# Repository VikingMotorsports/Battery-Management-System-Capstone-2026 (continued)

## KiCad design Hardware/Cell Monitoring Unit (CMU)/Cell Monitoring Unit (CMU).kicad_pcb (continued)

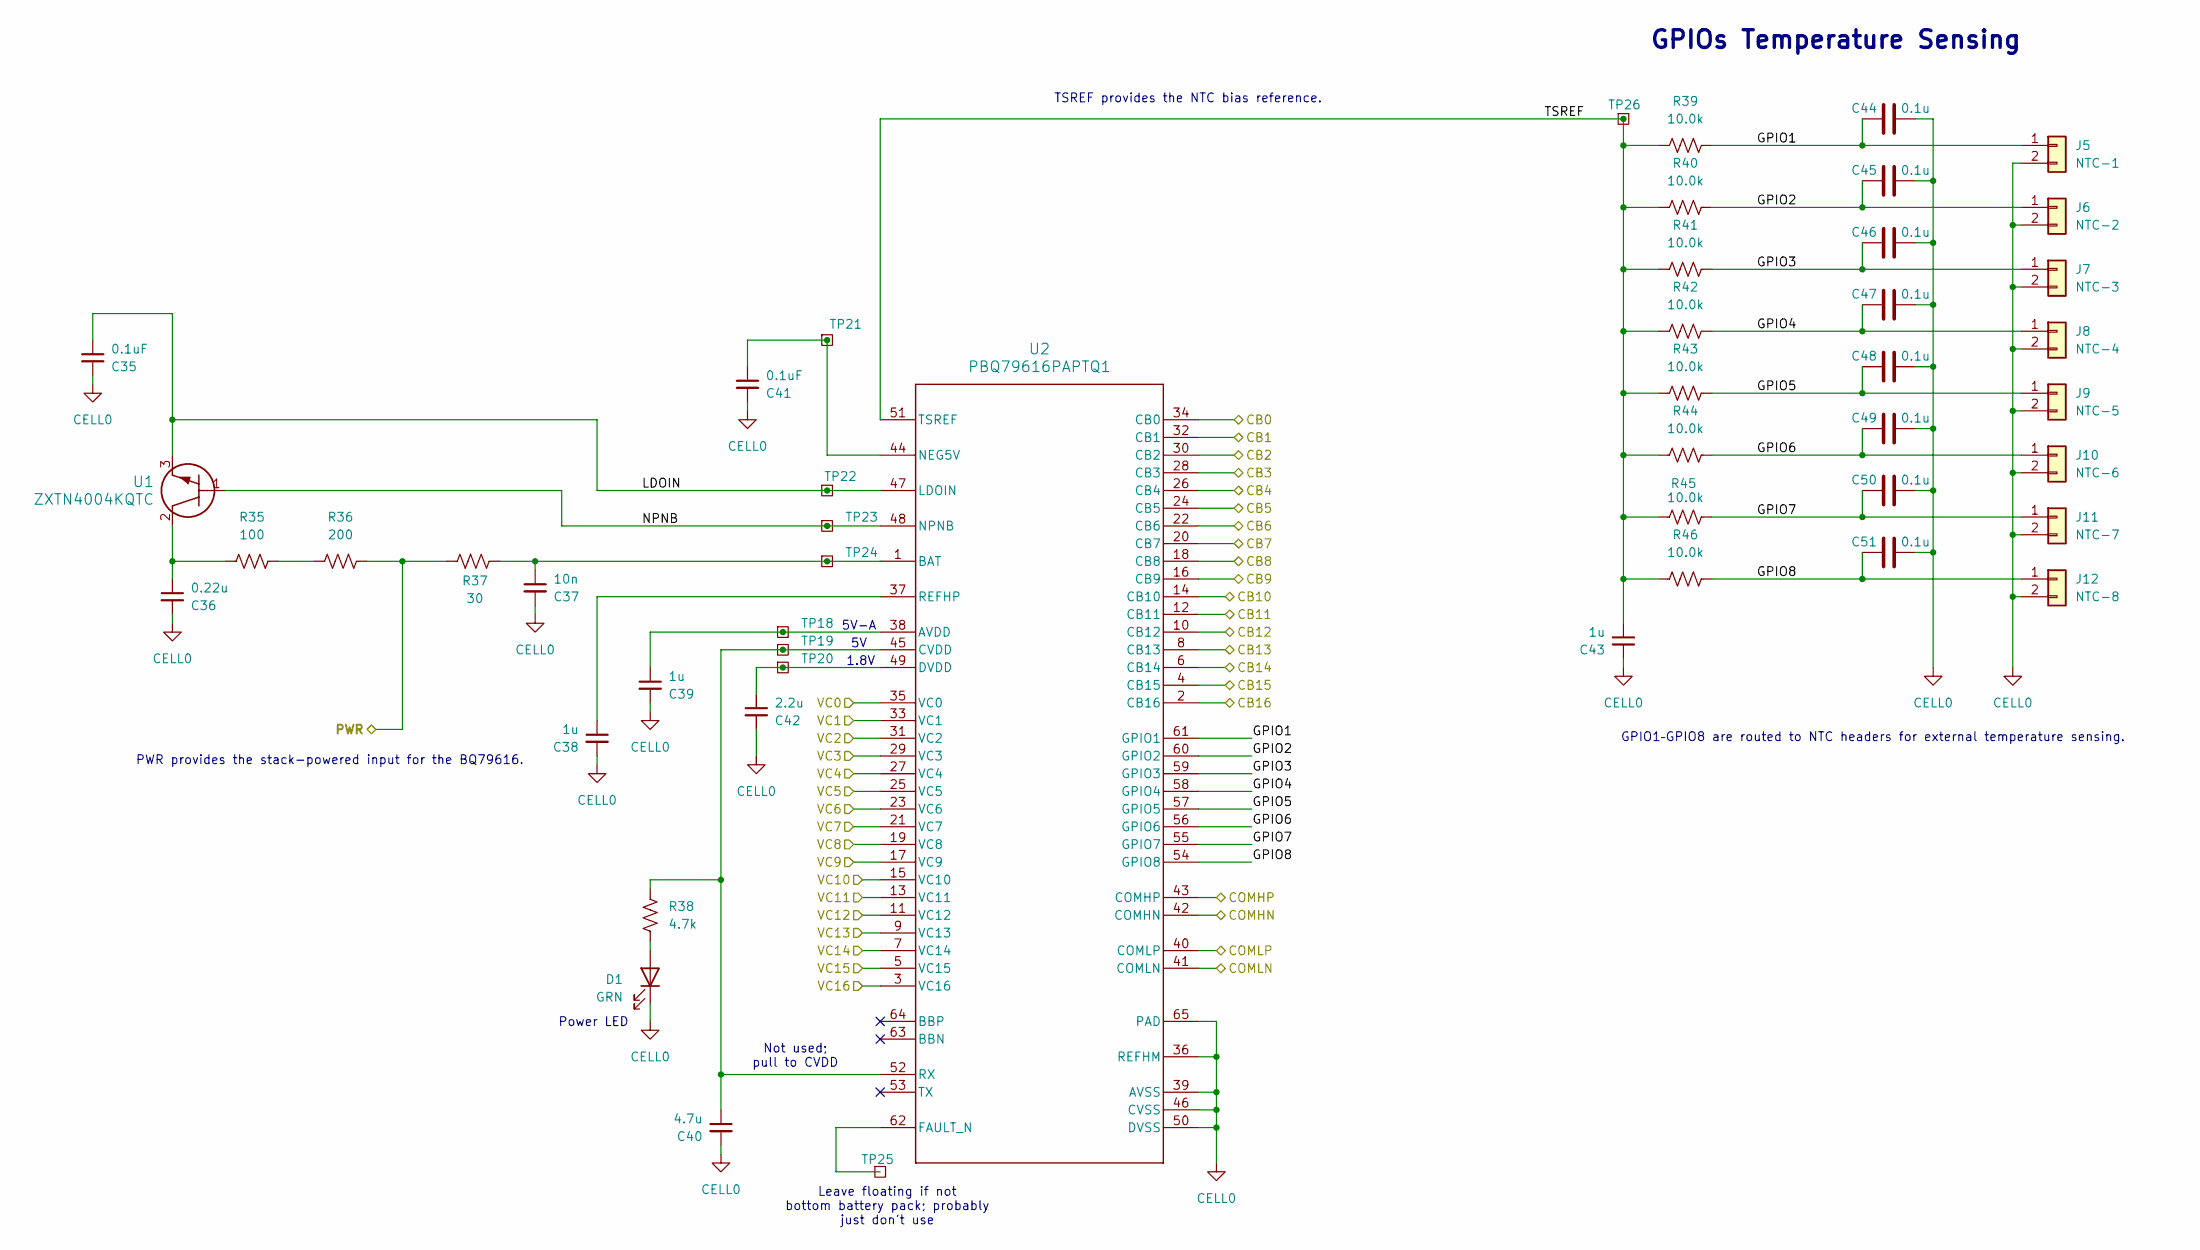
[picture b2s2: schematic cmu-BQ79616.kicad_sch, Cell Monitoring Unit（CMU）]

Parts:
C35, C41: 0.1uF; C_0805_2012Metric; MPN C0805X104K050T
C36: 0.22u; C_0805_2012Metric; MPN 885382207008
C37: 10n; C_0805_2012Metric; MPN C0805C103K5RECAUTO
C38, C39, C43: 1u; C_0805_2012Metric; MPN C0805C105K5RACTU
C40: 4.7u; C_0805_2012Metric; MPN C0805X475K025T
C42: 2.2u; C_0805_2012Metric; MPN 885012207079
C44, C45, C46, C47, C48, C49, C50, C51: 0.1u; C_0805_2012Metric; MPN C0805X104K050T
D1: GRN; LED_0805_2012Metric; MPN LTST-C170KGKT
J5: NTC-1; PinHeader_1x02_P2.54mm_Vertical; MPN 61300211121
J6: NTC-2; PinHeader_1x02_P2.54mm_Vertical; MPN 61300211121
J7: NTC-3; PinHeader_1x02_P2.54mm_Vertical; MPN 61300211121
J8: NTC-4; PinHeader_1x02_P2.54mm_Vertical; MPN 61300211121
J9: NTC-5; PinHeader_1x02_P2.54mm_Vertical; MPN 61300211121
J10: NTC-6; PinHeader_1x02_P2.54mm_Vertical; MPN 61300211121
J11: NTC-7; PinHeader_1x02_P2.54mm_Vertical; MPN 61300211121
J12: NTC-8; PinHeader_1x02_P2.54mm_Vertical; MPN 61300211121
R35: 100; R_2010_5025Metric; MPN RMCF2010FT100R
R36: 200; R_2010_5025Metric; MPN RMCF2010FT200R
R37: 30; R_2010_5025Metric; MPN RC2010FK-0730RL
R38: 4.7k; R_2010_5025Metric; MPN RC2010FK-074K7L
R39, R40, R41, R42, R43, R44, R45, R46: 10.0k; R_0805_2012Metric; MPN RC0805FR-0710KL
TP18, TP19, TP20, TP21, TP22, TP23, TP24, TP25, TP26: TestPoint_Square; TestPoint_THTPad_D1.5mm_Drill0.7mm
U1: ZXTN4004KQTC; DPAK_04KQTC_DIO; MPN ZXTN4004KQTC
U2: PBQ79616PAPTQ1; PAP0064F-IPC_A; MPN BQ79616PAPRQ1

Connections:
/CMU-BQ79616 AFE Core/CB0: U2.34 (CB0); also elsewhere on the board
/CMU-BQ79616 AFE Core/CB1: U2.32 (CB1); also elsewhere on the board
/CMU-BQ79616 AFE Core/CB2: U2.30 (CB2); also elsewhere on the board
/CMU-BQ79616 AFE Core/CB3: U2.28 (CB3); also elsewhere on the board
/CMU-BQ79616 AFE Core/CB4: U2.26 (CB4); also elsewhere on the board
/CMU-BQ79616 AFE Core/CB5: U2.24 (CB5); also elsewhere on the board
/CMU-BQ79616 AFE Core/CB6: U2.22 (CB6); also elsewhere on the board
/CMU-BQ79616 AFE Core/CB7: U2.20 (CB7); also elsewhere on the board
/CMU-BQ79616 AFE Core/CB8: U2.18 (CB8); also elsewhere on the board
/CMU-BQ79616 AFE Core/CB9: U2.16 (CB9); also elsewhere on the board
/CMU-BQ79616 AFE Core/CB10: U2.14 (CB10); also elsewhere on the board
/CMU-BQ79616 AFE Core/CB11: U2.12 (CB11); also elsewhere on the board
/CMU-BQ79616 AFE Core/CB12: U2.10 (CB12); also elsewhere on the board
/CMU-BQ79616 AFE Core/CB13: U2.8 (CB13); also elsewhere on the board
/CMU-BQ79616 AFE Core/CB14: U2.6 (CB14); also elsewhere on the board
/CMU-BQ79616 AFE Core/CB15: U2.4 (CB15); also elsewhere on the board
/CMU-BQ79616 AFE Core/CB16: U2.2 (CB16); also elsewhere on the board
/CMU-BQ79616 AFE Core/COMHN: U2.42 (COMHN); also elsewhere on the board
/CMU-BQ79616 AFE Core/COMHP: U2.43 (COMHP); also elsewhere on the board
/CMU-BQ79616 AFE Core/COMLN: U2.41 (COMLN); also elsewhere on the board
/CMU-BQ79616 AFE Core/COMLP: U2.40 (COMLP); also elsewhere on the board
/CMU-BQ79616 AFE Core/GPIO1: C44.1, J5.1, R39.2, U2.61 (GPIO1)
/CMU-BQ79616 AFE Core/GPIO2: C45.1, J6.1, R40.2, U2.60 (GPIO2)
/CMU-BQ79616 AFE Core/GPIO3: C46.1, J7.1, R41.2, U2.59 (GPIO3)
/CMU-BQ79616 AFE Core/GPIO4: C47.1, J8.1, R42.2, U2.58 (GPIO4)
/CMU-BQ79616 AFE Core/GPIO5: C48.1, J9.1, R43.2, U2.57 (GPIO5)
/CMU-BQ79616 AFE Core/GPIO6: C49.1, J10.1, R44.2, U2.56 (GPIO6)
/CMU-BQ79616 AFE Core/GPIO7: C50.1, J11.1, R45.2, U2.55 (GPIO7)
/CMU-BQ79616 AFE Core/GPIO8: C51.1, J12.1, R46.2, U2.54 (GPIO8)
/CMU-BQ79616 AFE Core/LDOIN: C35.1, TP22.1 (1_1), U1.3, U2.47 (LDOIN)
/CMU-BQ79616 AFE Core/NPNB: TP23.1 (1_1), U1.1, U2.48 (NPNB)
/CMU-BQ79616 AFE Core/PWR: R36.1, R37.1; also elsewhere on the board
/CMU-BQ79616 AFE Core/TSREF: C43.1, R39.1, R40.1, R41.1, R42.1, R43.1, R44.1, R45.1, R46.1, TP26.1 (1_1), U2.51 (TSREF)
/CMU-BQ79616 AFE Core/VC0: U2.35 (VC0); also elsewhere on the board
/CMU-BQ79616 AFE Core/VC1: U2.33 (VC1); also elsewhere on the board
/CMU-BQ79616 AFE Core/VC2: U2.31 (VC2); also elsewhere on the board
/CMU-BQ79616 AFE Core/VC3: U2.29 (VC3); also elsewhere on the board
/CMU-BQ79616 AFE Core/VC4: U2.27 (VC4); also elsewhere on the board
/CMU-BQ79616 AFE Core/VC5: U2.25 (VC5); also elsewhere on the board
/CMU-BQ79616 AFE Core/VC6: U2.23 (VC6); also elsewhere on the board
/CMU-BQ79616 AFE Core/VC7: U2.21 (VC7); also elsewhere on the board
/CMU-BQ79616 AFE Core/VC8: U2.19 (VC8); also elsewhere on the board
/CMU-BQ79616 AFE Core/VC9: U2.17 (VC9); also elsewhere on the board
/CMU-BQ79616 AFE Core/VC10: U2.15 (VC10); also elsewhere on the board
/CMU-BQ79616 AFE Core/VC11: U2.13 (VC11); also elsewhere on the board
/CMU-BQ79616 AFE Core/VC12: U2.11 (VC12); also elsewhere on the board
/CMU-BQ79616 AFE Core/VC13: U2.9 (VC13); also elsewhere on the board
/CMU-BQ79616 AFE Core/VC14: U2.7 (VC14); also elsewhere on the board
/CMU-BQ79616 AFE Core/VC15: U2.5 (VC15); also elsewhere on the board
/CMU-BQ79616 AFE Core/VC16: U2.3 (VC16); also elsewhere on the board
CELL0: C35.2, C36.2, C37.2, C38.2, C39.2, C40.2, C41.2, C42.2, C43.2, C44.2, C45.2, C46.2, C47.2, C48.2, C49.2, C50.2, C51.2, D1.1 (K), J5.2, J6.2, J7.2, J8.2, J9.2, J10.2, J11.2, J12.2, U2.36 (REFHM), U2.39 (AVSS), U2.46 (CVSS), U2.50 (DVSS), U2.65 (PAD); also elsewhere on the board
unnamed: C36.1, R35.2, U1.2
unnamed: D1.2 (A), R38.2
unnamed: R35.1, R36.2
unnamed: C39.1, TP18.1 (1_1), U2.38 (AVDD)
unnamed: C37.1, R37.2, TP24.1 (1_1), U2.1 (BAT)
unnamed: C40.1, R38.1, TP19.1 (1_1), U2.45 (CVDD), U2.52 (RX)
unnamed: C42.1, TP20.1 (1_1), U2.49 (DVDD)
unnamed: TP25.1 (1_1), U2.62 (FAULT_N)
unnamed: C41.1, TP21.1 (1_1), U2.44 (NEG5V)
unnamed: C38.1, U2.37 (REFHP)

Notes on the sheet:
1.8V
5V-A
Power LED
Leave floating if not bottom battery pack; probably just don't use
GPIOs Temperature Sensing
PWR provides the stack-powered input for the BQ79616.
Not used; pull to CVDD
GPIO1–GPIO8 are routed to NTC headers for external temperature sensing.
TSREF provides the NTC bias reference.

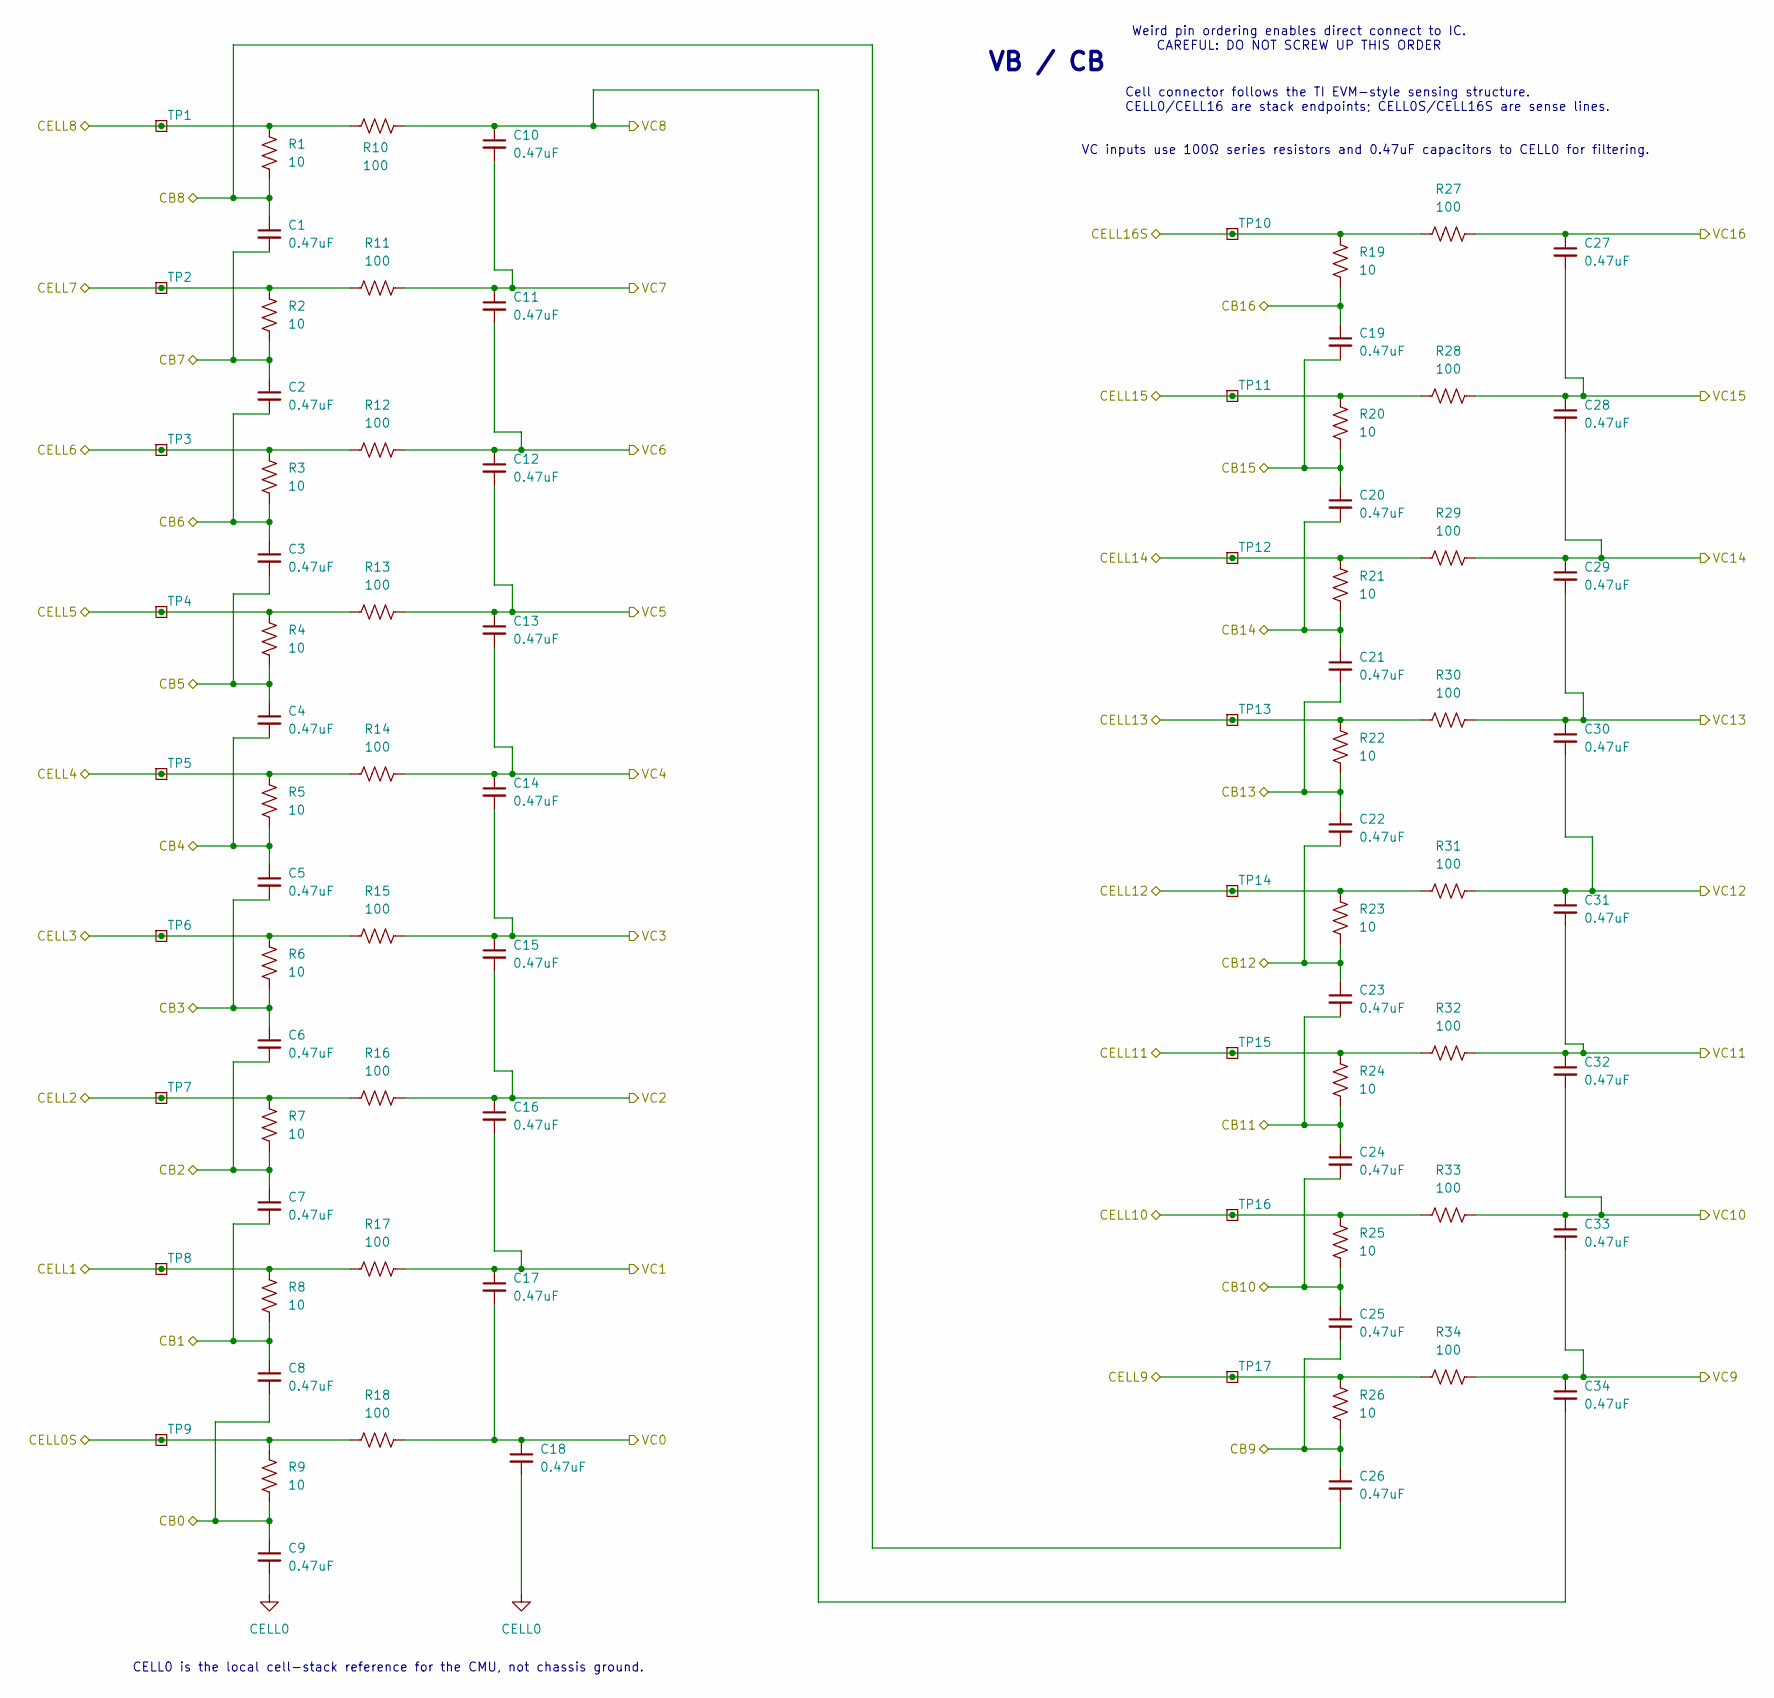
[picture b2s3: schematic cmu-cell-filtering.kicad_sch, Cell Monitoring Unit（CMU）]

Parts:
C1, C2, C3, C4, C5, C6, C7, C8, C9, C10, C11, C12, C13, C14, C15, C16, C17, C18, C19, C20, C21, C22, C23, C24, C25, C26, C27, C28, C29, C30, C31, C32, C33, C34: 0.47uF; C_0805_2012Metric; MPN CS0805KKX7R9BB474
R1, R2, R3, R4, R5, R6, R7, R8, R9, R19, R20, R21, R22, R23, R24, R25, R26: 10; R_1210_3225Metric; MPN RC1210FR-0710RL
R10, R11, R12, R13, R14, R15, R16, R17, R18, R27, R28, R29, R30, R31, R32, R33, R34: 100; R_0805_2012Metric; MPN RC0805FR-07100RL
TP1, TP2, TP3, TP4, TP5, TP6, TP7, TP8, TP9, TP10, TP11, TP12, TP13, TP14, TP15, TP16, TP17: TestPoint_Square; TestPoint_THTPad_D1.5mm_Drill0.7mm

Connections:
/CELL0S: R9.1, R18.1, TP9.1 (1_1); also elsewhere on the board
/CMU-BQ79616 AFE Core/CB0: C8.2, C9.1, R9.2; also elsewhere on the board
/CMU-BQ79616 AFE Core/CB1: C7.2, C8.1, R8.2; also elsewhere on the board
/CMU-BQ79616 AFE Core/CB2: C6.2, C7.1, R7.2; also elsewhere on the board
/CMU-BQ79616 AFE Core/CB3: C5.2, C6.1, R6.2; also elsewhere on the board
/CMU-BQ79616 AFE Core/CB4: C4.2, C5.1, R5.2; also elsewhere on the board
/CMU-BQ79616 AFE Core/CB5: C3.2, C4.1, R4.2; also elsewhere on the board
/CMU-BQ79616 AFE Core/CB6: C2.2, C3.1, R3.2; also elsewhere on the board
/CMU-BQ79616 AFE Core/CB7: C1.2, C2.1, R2.2; also elsewhere on the board
/CMU-BQ79616 AFE Core/CB8: C1.1, C26.2, R1.2; also elsewhere on the board
/CMU-BQ79616 AFE Core/CB9: C25.2, C26.1, R26.2; also elsewhere on the board
/CMU-BQ79616 AFE Core/CB10: C24.2, C25.1, R25.2; also elsewhere on the board
/CMU-BQ79616 AFE Core/CB11: C23.2, C24.1, R24.2; also elsewhere on the board
/CMU-BQ79616 AFE Core/CB12: C22.2, C23.1, R23.2; also elsewhere on the board
/CMU-BQ79616 AFE Core/CB13: C21.2, C22.1, R22.2; also elsewhere on the board
/CMU-BQ79616 AFE Core/CB14: C20.2, C21.1, R21.2; also elsewhere on the board
/CMU-BQ79616 AFE Core/CB15: C19.2, C20.1, R20.2; also elsewhere on the board
/CMU-BQ79616 AFE Core/CB16: C19.1, R19.2; also elsewhere on the board
/CMU-BQ79616 AFE Core/VC0: C17.2, C18.1, R18.2; also elsewhere on the board
/CMU-BQ79616 AFE Core/VC1: C16.2, C17.1, R17.2; also elsewhere on the board
/CMU-BQ79616 AFE Core/VC2: C15.2, C16.1, R16.2; also elsewhere on the board
/CMU-BQ79616 AFE Core/VC3: C14.2, C15.1, R15.2; also elsewhere on the board
/CMU-BQ79616 AFE Core/VC4: C13.2, C14.1, R14.2; also elsewhere on the board
/CMU-BQ79616 AFE Core/VC5: C12.2, C13.1, R13.2; also elsewhere on the board
/CMU-BQ79616 AFE Core/VC6: C11.2, C12.1, R12.2; also elsewhere on the board
/CMU-BQ79616 AFE Core/VC7: C10.2, C11.1, R11.2; also elsewhere on the board
/CMU-BQ79616 AFE Core/VC8: C10.1, C34.2, R10.2; also elsewhere on the board
/CMU-BQ79616 AFE Core/VC9: C33.2, C34.1, R34.2; also elsewhere on the board
/CMU-BQ79616 AFE Core/VC10: C32.2, C33.1, R33.2; also elsewhere on the board
/CMU-BQ79616 AFE Core/VC11: C31.2, C32.1, R32.2; also elsewhere on the board
/CMU-BQ79616 AFE Core/VC12: C30.2, C31.1, R31.2; also elsewhere on the board
/CMU-BQ79616 AFE Core/VC13: C29.2, C30.1, R30.2; also elsewhere on the board
/CMU-BQ79616 AFE Core/VC14: C28.2, C29.1, R29.2; also elsewhere on the board
/CMU-BQ79616 AFE Core/VC15: C27.2, C28.1, R28.2; also elsewhere on the board
/CMU-BQ79616 AFE Core/VC16: C27.1, R27.2; also elsewhere on the board
/CMU-Cell Filtering & Balancing/CELL1: R8.1, R17.1, TP8.1 (1_1); also elsewhere on the board
/CMU-Cell Filtering & Balancing/CELL2: R7.1, R16.1, TP7.1 (1_1); also elsewhere on the board
/CMU-Cell Filtering & Balancing/CELL3: R6.1, R15.1, TP6.1 (1_1); also elsewhere on the board
/CMU-Cell Filtering & Balancing/CELL4: R5.1, R14.1, TP5.1 (1_1); also elsewhere on the board
/CMU-Cell Filtering & Balancing/CELL5: R4.1, R13.1, TP4.1 (1_1); also elsewhere on the board
/CMU-Cell Filtering & Balancing/CELL6: R3.1, R12.1, TP3.1 (1_1); also elsewhere on the board
/CMU-Cell Filtering & Balancing/CELL7: R2.1, R11.1, TP2.1 (1_1); also elsewhere on the board
/CMU-Cell Filtering & Balancing/CELL8: R1.1, R10.1, TP1.1 (1_1); also elsewhere on the board
/CMU-Cell Filtering & Balancing/CELL9: R26.1, R34.1, TP17.1 (1_1); also elsewhere on the board
/CMU-Cell Filtering & Balancing/CELL10: R25.1, R33.1, TP16.1 (1_1); also elsewhere on the board
/CMU-Cell Filtering & Balancing/CELL11: R24.1, R32.1, TP15.1 (1_1); also elsewhere on the board
/CMU-Cell Filtering & Balancing/CELL12: R23.1, R31.1, TP14.1 (1_1); also elsewhere on the board
/CMU-Cell Filtering & Balancing/CELL13: R22.1, R30.1, TP13.1 (1_1); also elsewhere on the board
/CMU-Cell Filtering & Balancing/CELL14: R21.1, R29.1, TP12.1 (1_1); also elsewhere on the board
/CMU-Cell Filtering & Balancing/CELL15: R20.1, R28.1, TP11.1 (1_1); also elsewhere on the board
/CMU-Cell Filtering & Balancing/CELL16S: R19.1, R27.1, TP10.1 (1_1); also elsewhere on the board
CELL0: C9.2, C18.2; also elsewhere on the board

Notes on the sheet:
CELL0 is the local cell-stack reference for the CMU, not chassis ground.
VC inputs use 100Ω series resistors and 0.47uF capacitors to CELL0 for filtering.
Cell connector follows the TI EVM-style sensing structure. CELL0/CELL16 are stack endpoints; CELL0S/CELL16S are sense lines.
Weird pin ordering enables direct connect to IC. CAREFUL: DO NOT SCREW UP THIS ORDER
VB / CB

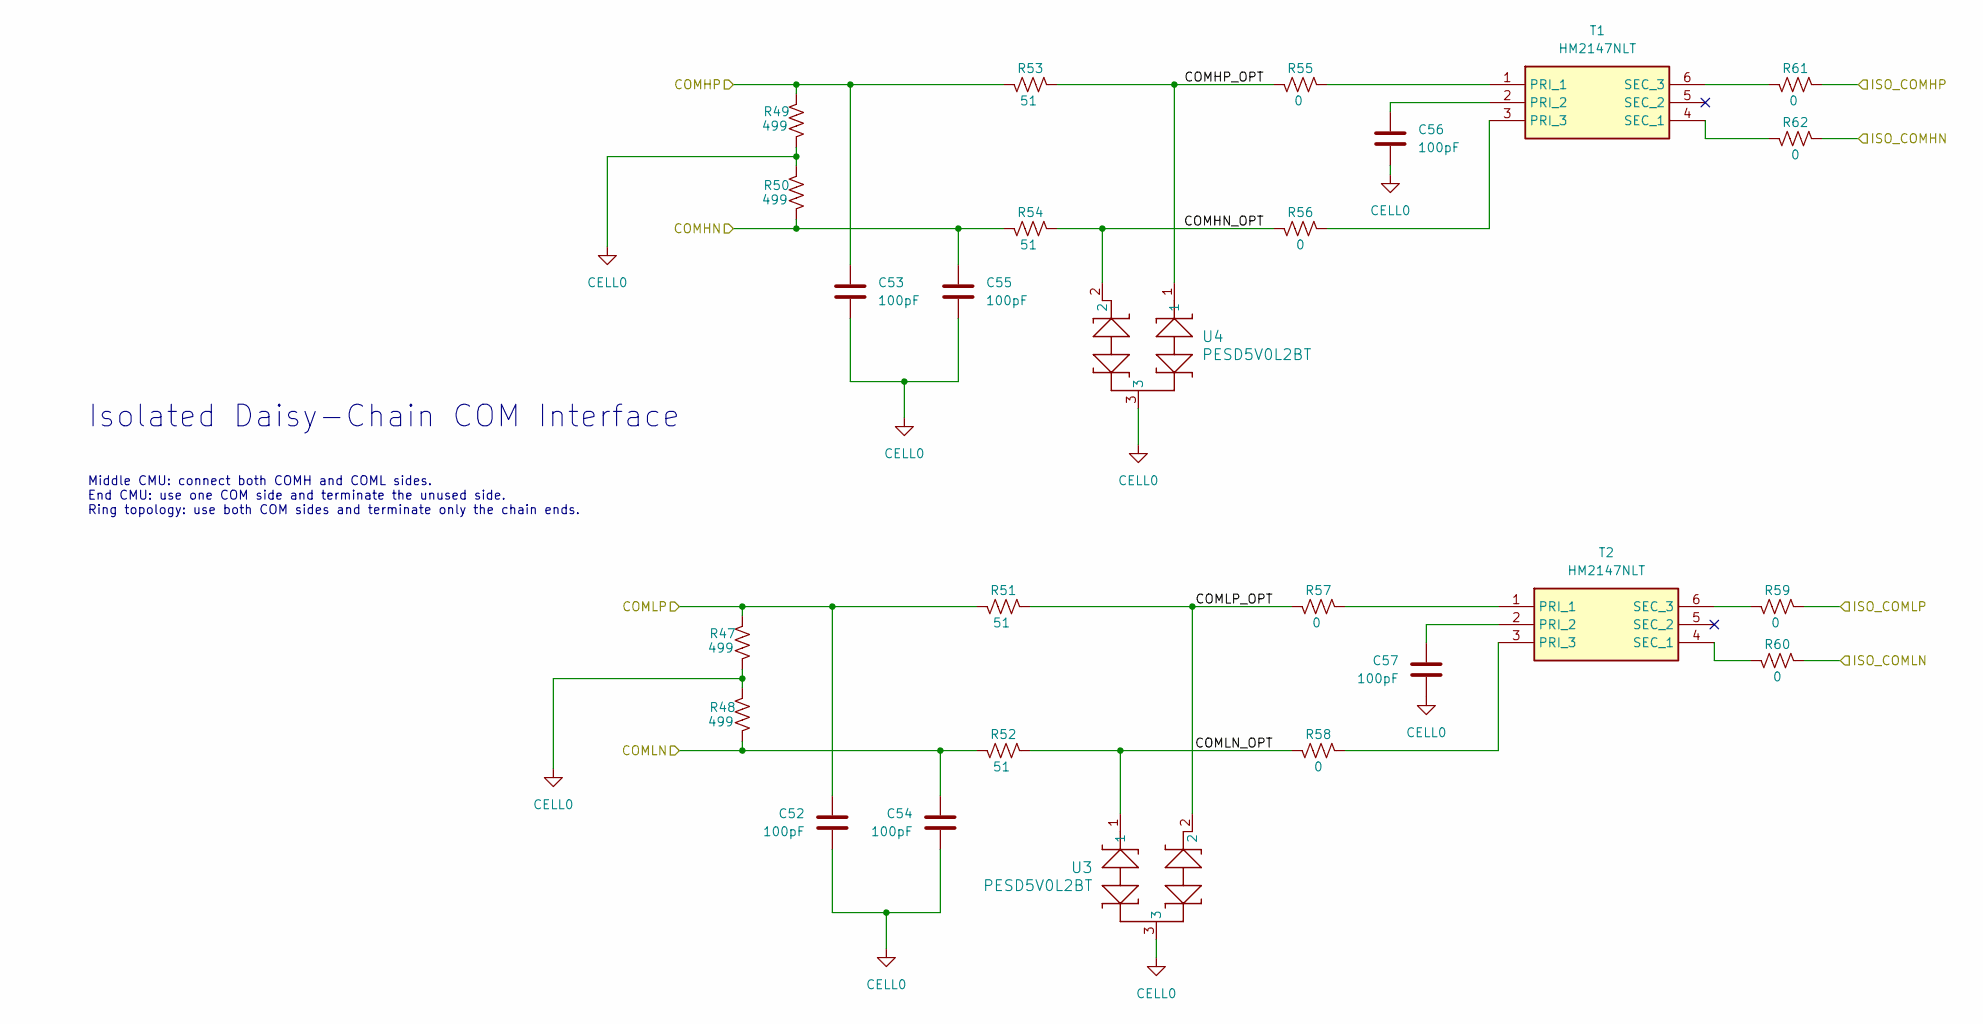
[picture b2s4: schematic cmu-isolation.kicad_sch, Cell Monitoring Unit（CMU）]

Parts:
C52, C53, C54, C55, C56, C57: 100pF; C_0805_2012Metric; MPN CC0805KRNPO9BN101
R47, R48, R49, R50: 499; R_0805_2012Metric; MPN RC0805FR-07499RL
R51, R52, R53, R54: 51; R_0805_2012Metric; MPN RC0805FR-0751RL
R55, R56, R57, R58, R59, R60, R61, R62: 0; R_0805_2012Metric; MPN RC0805JR-070RL
T1, T2: HM2147NLT; Manufacturer_Part_Number HM2147NLT; Mouser Part Number 673-HM2147NLT
U3, U4: PESD5V0L2BT; SOT23_NEX; MPN PESD5V0L2BT,215

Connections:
/CMU-BQ79616 AFE Core/COMHN: C55.1, R50.2, R54.2; also elsewhere on the board
/CMU-BQ79616 AFE Core/COMHP: C53.1, R49.1, R53.2; also elsewhere on the board
/CMU-BQ79616 AFE Core/COMLN: C54.1, R48.2, R52.2; also elsewhere on the board
/CMU-BQ79616 AFE Core/COMLP: C52.1, R47.1, R51.2; also elsewhere on the board
/CMU-Daisy-Chain Interface/COMHN_OPT: R54.1, R56.2, U4.2
/CMU-Daisy-Chain Interface/COMHP_OPT: R53.1, R55.2, U4.1
/CMU-Daisy-Chain Interface/COMLN_OPT: R52.1, R58.2, U3.1
/CMU-Daisy-Chain Interface/COMLP_OPT: R51.1, R57.2, U3.2
/CMU-Daisy-Chain Interface/ISO_COMHN: R62.1; also elsewhere on the board
/CMU-Daisy-Chain Interface/ISO_COMHP: R61.1; also elsewhere on the board
/CMU-Daisy-Chain Interface/ISO_COMLN: R60.1; also elsewhere on the board
/CMU-Daisy-Chain Interface/ISO_COMLP: R59.1; also elsewhere on the board
CELL0: C52.2, C53.2, C54.2, C55.2, C56.2, C57.2, R47.2, R48.1, R49.2, R50.1, U3.3, U4.3; also elsewhere on the board
unnamed: R55.1, T1.1 (PRI_1)
unnamed: C56.1, T1.2 (PRI_2)
unnamed: R56.1, T1.3 (PRI_3)
unnamed: R62.2, T1.4 (SEC_1)
unnamed: R61.2, T1.6 (SEC_3)
unnamed: R57.1, T2.1 (PRI_1)
unnamed: C57.1, T2.2 (PRI_2)
unnamed: R58.1, T2.3 (PRI_3)
unnamed: R60.2, T2.4 (SEC_1)
unnamed: R59.2, T2.6 (SEC_3)

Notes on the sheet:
Isolated Daisy-Chain COM Interface
Middle CMU: connect both COMH and COML sides. End CMU: use one COM side and terminate the unused side. Ring topology: use both COM sides and terminate only the chain ends.

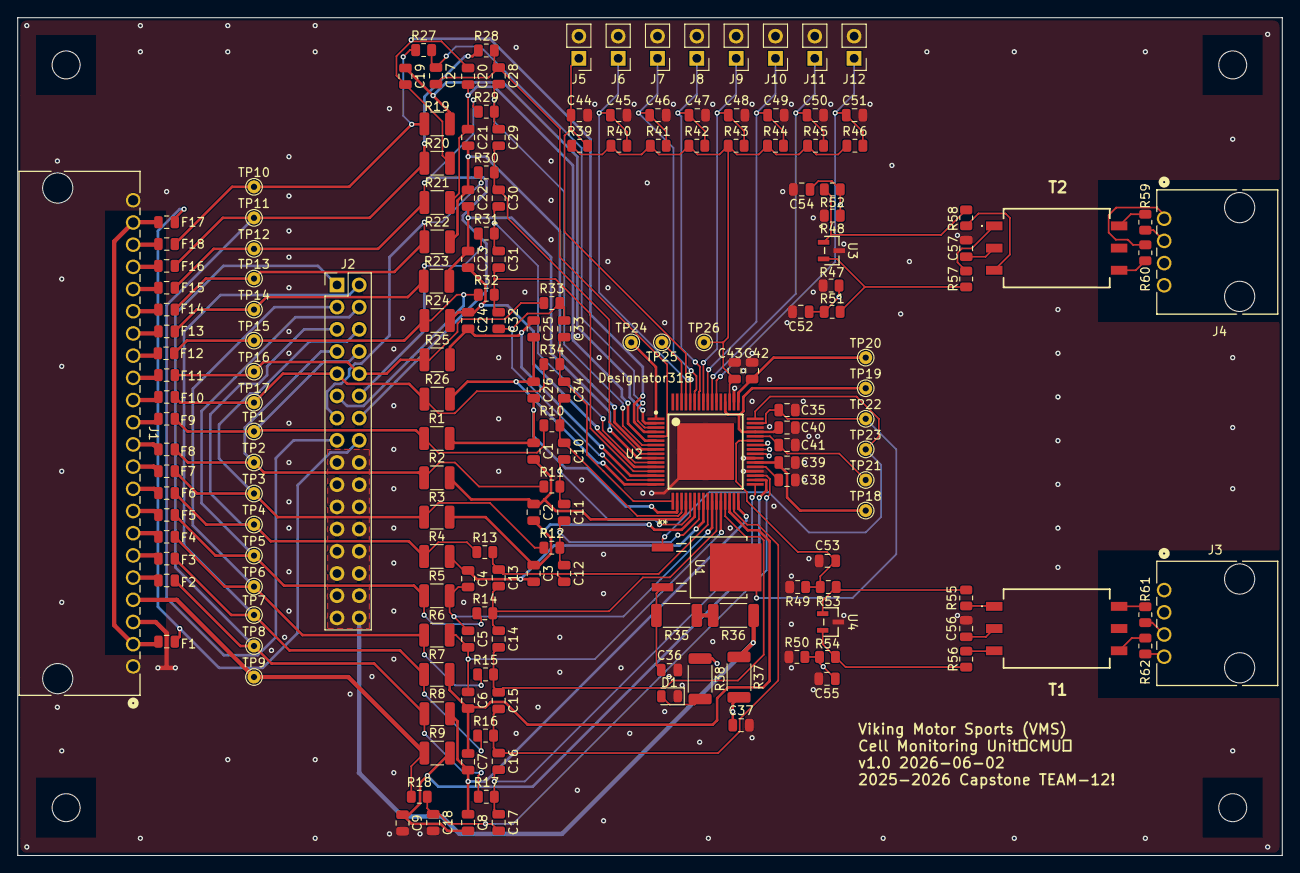
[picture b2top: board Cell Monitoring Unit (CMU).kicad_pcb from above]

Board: 4 copper layers, 144.7 x 95.9 mm, 182 parts (0 on the bottom side), 114 nets.

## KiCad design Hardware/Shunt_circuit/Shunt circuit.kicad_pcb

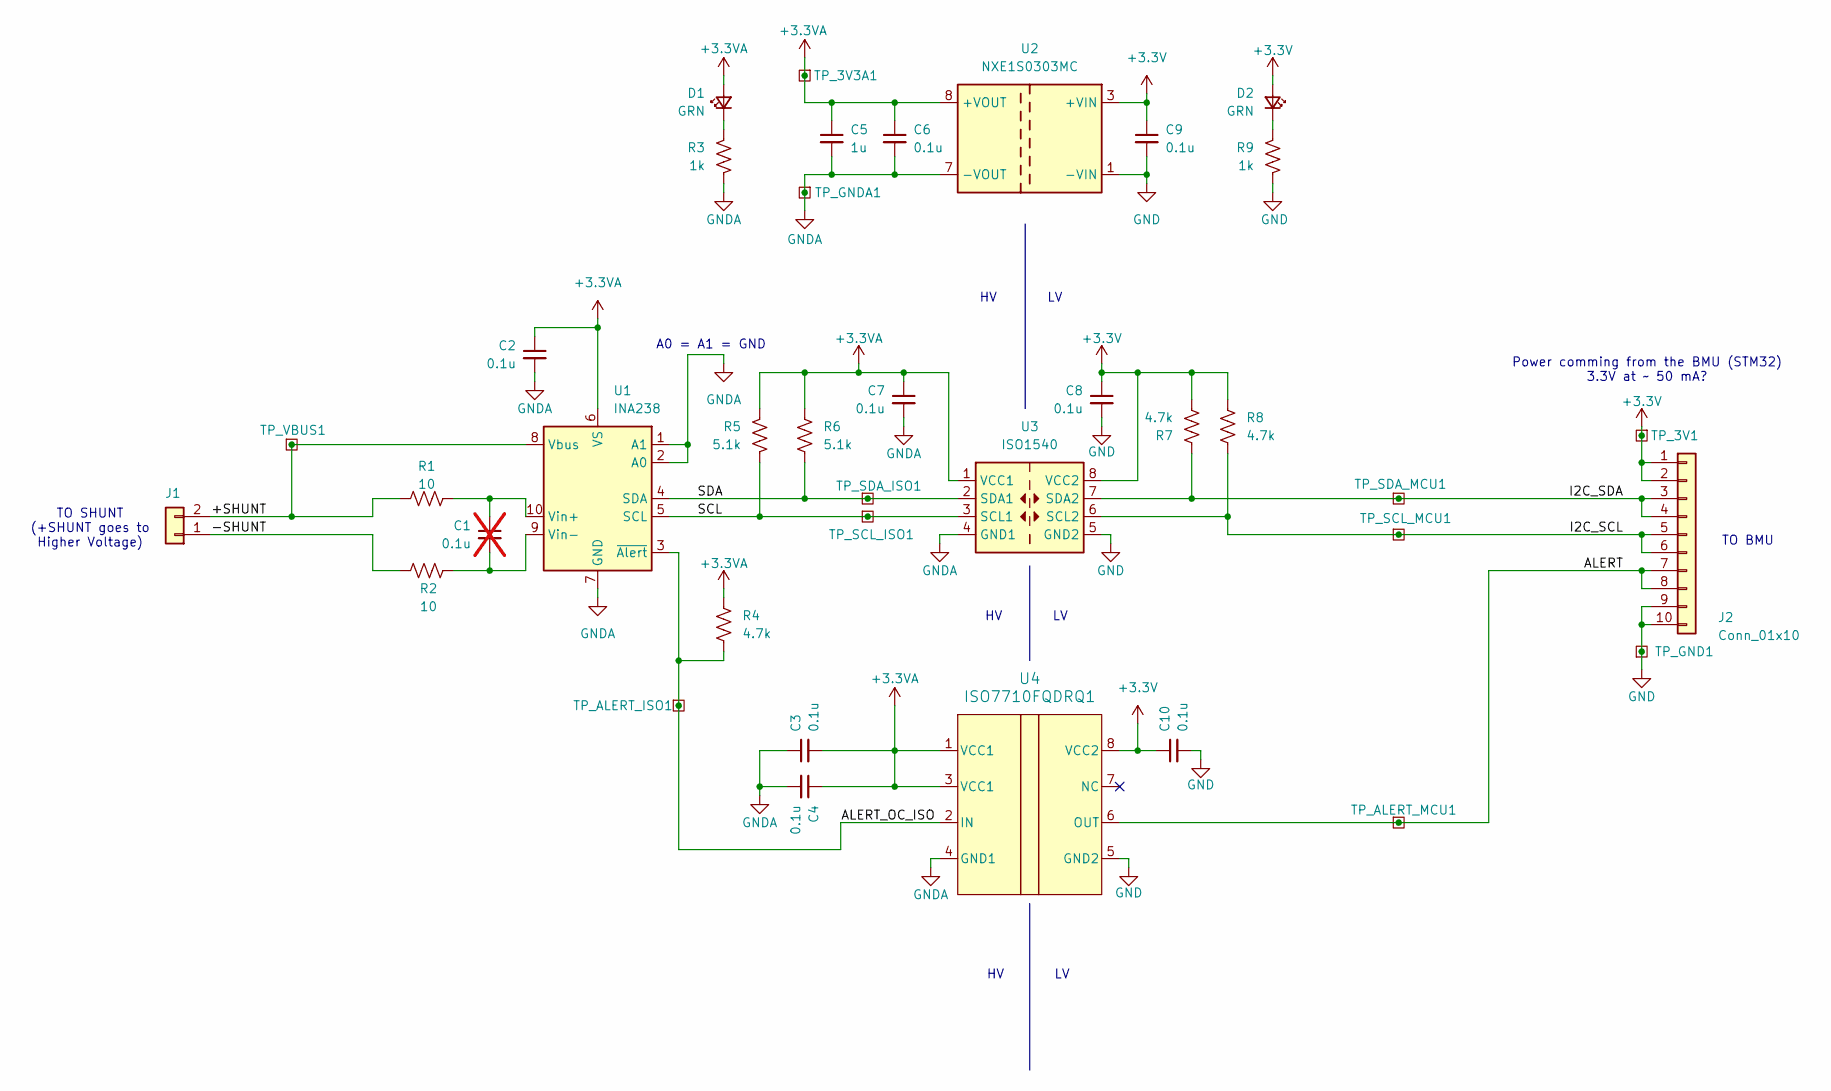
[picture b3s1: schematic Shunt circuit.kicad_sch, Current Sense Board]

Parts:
C1: 0.1u; C_0805_2012Metric; not fitted
C2, C3, C4, C6, C7, C8, C9, C10: 0.1u; C_0805_2012Metric; MPN CC0805KRX7R9BB104
C5: 1u; C_0805_2012Metric; MPN CC0805KKX7R7BB105
D1: GRN; LED_0805_2012Metric; MPN LTST-C170KRKT
D2: GRN; LED_0805_2012Metric; MPN LTST-C170GKT
J1: Shunt Voltage Measuring Points; TerminalBlock_Phoenix_MKDS-1,5-2-5.08_1x02_P5.08mm_Horizont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; MPN 1715721
J2: Conn_01x10; PinHeader_1x10_P2.54mm_Vertical; MPN PRPC010SAAN-RC
R1, R2: 10; R_0805_2012Metric; MPN RC0805FR-0710RL
R3, R9: 1k; R_0805_2012Metric; MPN RC0805FR-071KL
R4, R7, R8: 4.7k; R_0805_2012Metric; MPN RC0805FR-074K7L
R5, R6: 5.1k; R_0805_2012Metric; MPN RC0805FR-075K1L
TP_3V1, TP_3V3A1: TestPoint_Square; TestPoint_Pad_1.0x1.0mm
TP_ALERT_ISO1: TestPoint_Square; TestPoint_Pad_1.0x1.0mm
TP_ALERT_MCU1: TestPoint_Square; TestPoint_Pad_1.0x1.0mm
TP_GND1: TestPoint_Square; TestPoint_Pad_1.0x1.0mm
TP_GNDA1: TestPoint_Square; TestPoint_Pad_1.0x1.0mm
TP_SCL_ISO1: TestPoint_Square; TestPoint_Pad_1.0x1.0mm
TP_SCL_MCU1: TestPoint_Square; TestPoint_Pad_1.0x1.0mm
TP_SDA_ISO1: TestPoint_Square; TestPoint_Pad_1.0x1.0mm
TP_SDA_MCU1: TestPoint_Square; TestPoint_Pad_1.0x1.0mm
TP_VBUS1: TestPoint_Square; TestPoint_Pad_1.0x1.0mm
U1: INA238; TSSOP-10_3x3mm_P0.5mm; MPN INA238AQDGSRQ1
U2: NXE1S0303MC; Converter_DCDC_Murata_NXExSxxxxMC_SMD; MPN NXF1S0303MC-R7
U3: ISO1540; SOIC-8_3.9x4.9mm_P1.27mm; MPN ISO1540QDRQ1
U4: ISO7710FQDRQ1; D0008B_N; MPN ISO7710FQDRQ1

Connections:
+3.3V: C8.1, C9.1, C10.1, D2.2 (A), J2.1, J2.2, R7.2, R8.1, TP_3V1.1 (1_1), U2.3 (+VIN), U3.8 (VCC2), U4.8 (VCC2)
+3.3VA: C2.1, C3.2, C4.1, C5.1, C6.1, C7.1, D1.2 (A), R4.2, R5.1, R6.1, TP_3V3A1.1 (1_1), U1.6 (VS), U2.8 (+VOUT), U3.1 (VCC1), U4.1 (VCC1), U4.3 (VCC1)
/+SHUNT: J1.2, R1.1, TP_VBUS1.1 (1_1), U1.8 (Vbus)
/-SHUNT: J1.1, R2.1
/ALERT: J2.7, J2.8, TP_ALERT_MCU1.1 (1_1), U4.6 (OUT)
/ALERT_OC_ISO: R4.1, TP_ALERT_ISO1.1 (1_1), U1.3 (~Alert), U4.2 (IN)
/I2C_SCL: J2.5, J2.6, R8.2, TP_SCL_MCU1.1 (1_1), U3.6 (SCL2)
/I2C_SDA: J2.3, J2.4, R7.1, TP_SDA_MCU1.1 (1_1), U3.7 (SDA2)
/SCL: R5.2, TP_SCL_ISO1.1 (1_1), U1.5 (SCL), U3.3 (SCL1)
/SDA: R6.2, TP_SDA_ISO1.1 (1_1), U1.4 (SDA), U3.2 (SDA1)
GND: C8.2, C9.2, C10.2, J2.9, J2.10, R9.2, TP_GND1.1 (1_1), U2.1 (-VIN), U3.5 (GND2), U4.5 (GND2)
GNDA: C2.2, C3.1, C4.2, C5.2, C6.2, C7.2, R3.2, TP_GNDA1.1 (1_1), U1.1 (A1), U1.2 (A0), U1.7 (GND), U2.7 (-VOUT), U3.4 (GND1), U4.4 (GND1)
unnamed: D1.1 (K), R3.1
unnamed: D2.1 (K), R9.1
unnamed: C1.1, R1.2, U1.10 (Vin+)
unnamed: C1.2, R2.2, U1.9 (Vin-)

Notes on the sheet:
Power comming from the BMU (STM32) 3.3V at ~ 50 mA?
TO SHUNT (+SHUNT goes to Higher Voltage)
TO BMU
A0 = A1 = GND

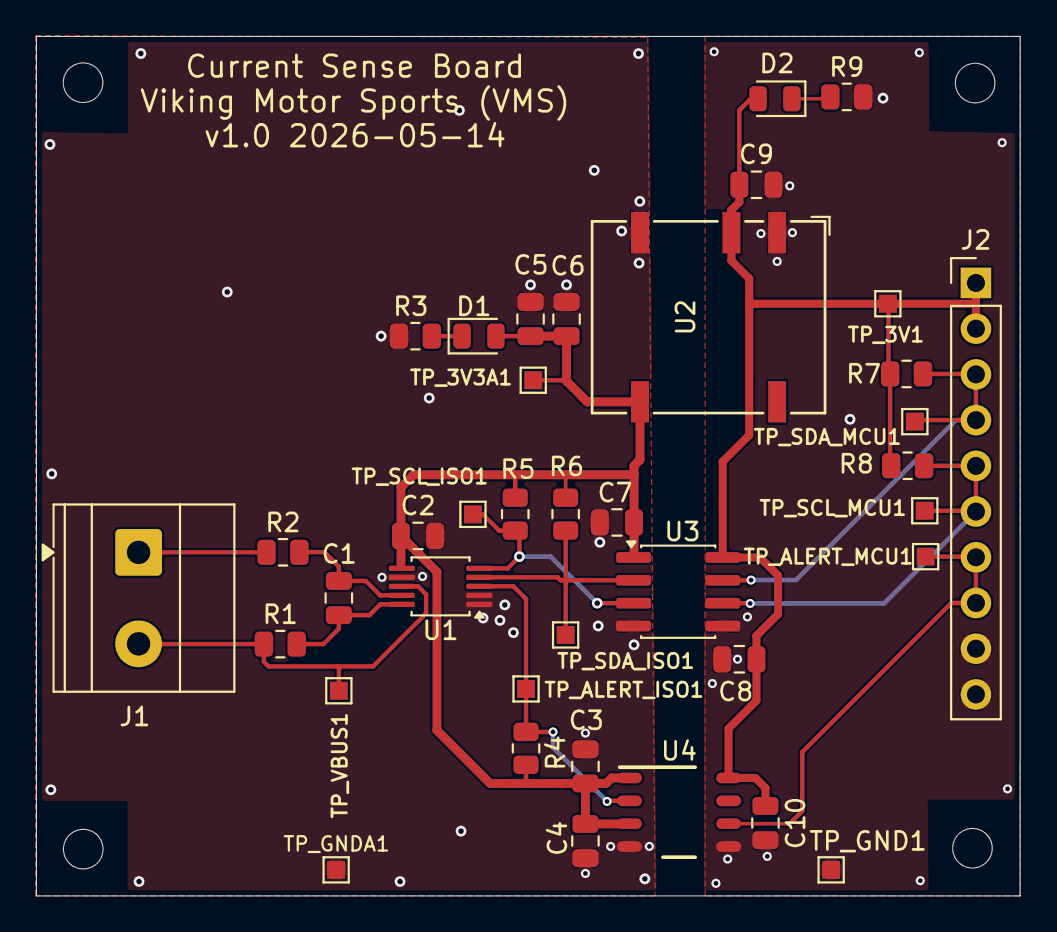
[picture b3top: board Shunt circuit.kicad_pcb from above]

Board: 2 copper layers, 54.7 x 47.8 mm, 38 parts (0 on the bottom side), 16 nets.
